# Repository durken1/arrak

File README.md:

# arrak
( unnecessarily weird) 36 key ergo keyboard

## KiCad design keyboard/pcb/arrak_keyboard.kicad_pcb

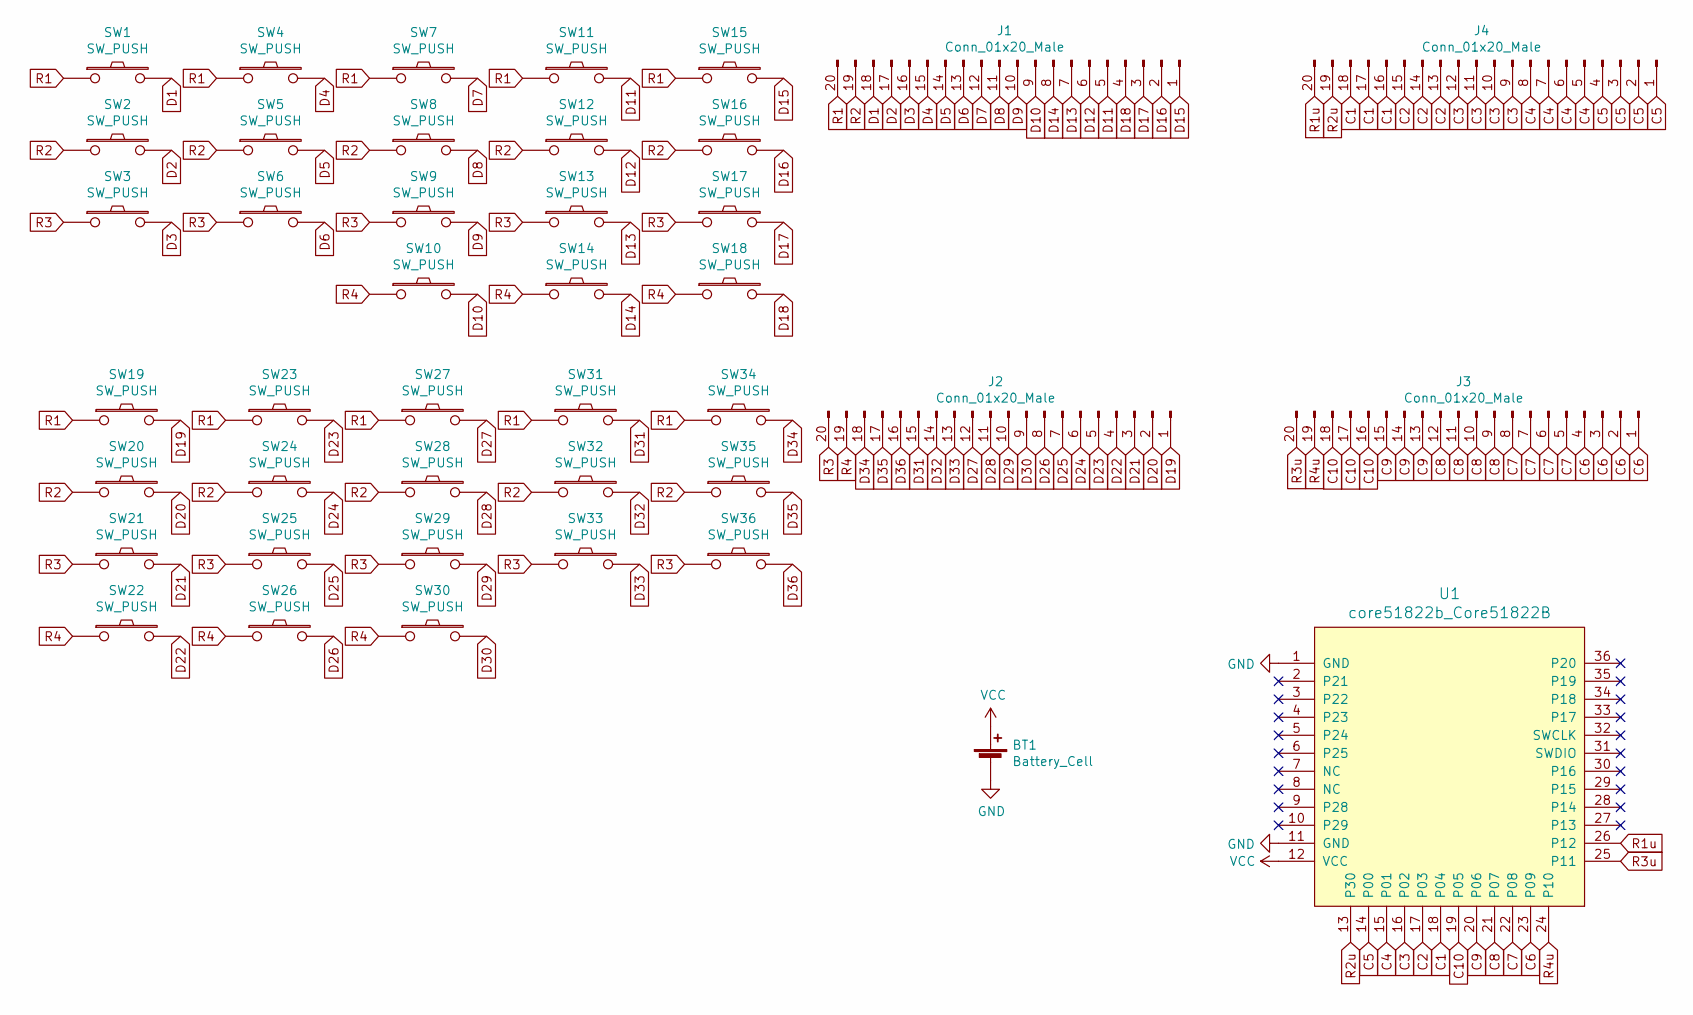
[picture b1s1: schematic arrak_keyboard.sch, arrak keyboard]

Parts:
BT1: Battery_Cell; BatteryHolder_Keystone_3034_1x20mm
J1, J2, J3, J4: Conn_01x20_Male; PinHeader_1x20_P2.54mm_Vertical
SW1, SW2, SW3, SW4, SW5, SW6, SW7, SW8, SW9, SW10, SW11, SW12, SW13, SW14, SW15, SW16, SW17, SW18, SW19, SW20, SW21, SW22, SW23, SW24, SW25, SW26, SW27, SW28, SW29, SW30, SW31, SW32, SW33, SW34, SW35, SW36: SW_PUSH; Kailh-PG1350-1u-reversible-NoLED
U1: core51822b_Core51822B; MY-YJ-14015-Module

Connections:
C1: J4.16, J4.17, J4.18, U1.18 (P04)
C2: J4.13, J4.14, J4.15, U1.17 (P03)
C3: J4.9, J4.10, J4.11, J4.12, U1.16 (P02)
C4: J4.5, J4.6, J4.7, J4.8, U1.15 (P01)
C5: J4.1, J4.2, J4.3, J4.4, U1.14 (P00)
C6: J3.1, J3.2, J3.3, J3.4, U1.23 (P09)
C7: J3.5, J3.6, J3.7, J3.8, U1.22 (P08)
C8: J3.9, J3.10, J3.11, J3.12, U1.21 (P07)
C9: J3.13, J3.14, J3.15, U1.20 (P06)
C10: J3.16, J3.17, J3.18, U1.19 (P05)
D1: J1.18, SW1.2
D2: J1.17, SW2.2
D3: J1.16, SW3.2
D4: J1.15, SW4.2
D5: J1.14, SW5.2
D6: J1.13, SW6.2
D7: J1.12, SW7.2
D8: J1.11, SW8.2
D9: J1.10, SW9.2
D10: J1.9, SW10.2
D11: J1.5, SW11.2
D12: J1.6, SW12.2
D13: J1.7, SW13.2
D14: J1.8, SW14.2
D15: J1.1, SW15.2
D16: J1.2, SW16.2
D17: J1.3, SW17.2
D18: J1.4, SW18.2
D19: J2.1, SW19.2
D20: J2.2, SW20.2
D21: J2.3, SW21.2
D22: J2.4, SW22.2
D23: J2.5, SW23.2
D24: J2.6, SW24.2
D25: J2.7, SW25.2
D26: J2.8, SW26.2
D27: J2.12, SW27.2
D28: J2.11, SW28.2
D29: J2.10, SW29.2
D30: J2.9, SW30.2
D31: J2.15, SW31.2
D32: J2.14, SW32.2
D33: J2.13, SW33.2
D34: J2.18, SW34.2
D35: J2.17, SW35.2
D36: J2.16, SW36.2
GND: BT1.2 (-), U1.1 (GND), U1.11 (GND)
R1: J1.20, SW1.1, SW4.1, SW7.1, SW11.1, SW15.1, SW19.1, SW23.1, SW27.1, SW31.1, SW34.1
R1u: J4.20, U1.26 (P12)
R2: J1.19, SW2.1, SW5.1, SW8.1, SW12.1, SW16.1, SW20.1, SW24.1, SW28.1, SW32.1, SW35.1
R2u: J4.19, U1.13 (P30)
R3: J2.20, SW3.1, SW6.1, SW9.1, SW13.1, SW17.1, SW21.1, SW25.1, SW29.1, SW33.1, SW36.1
R3u: J3.20, U1.25 (P11)
R4: J2.19, SW10.1, SW14.1, SW18.1, SW22.1, SW26.1, SW30.1
R4u: J3.19, U1.24 (P10)
VCC: BT1.1 (+), U1.12 (VCC)

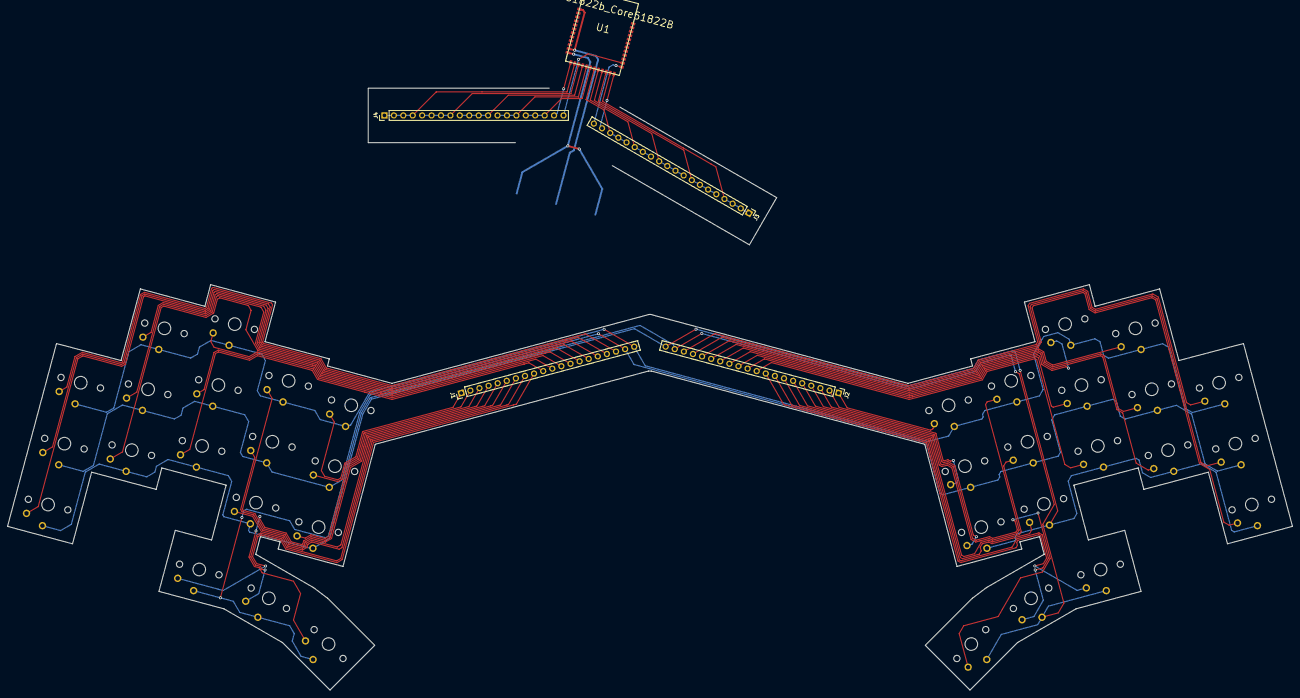
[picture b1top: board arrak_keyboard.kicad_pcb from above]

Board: 2 copper layers, 346.3 x 109.3 mm, 42 parts (1 on the bottom side), 56 nets.

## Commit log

2021-08-13 placement of switch footprints complete
2021-09-01 finish physical layout of keyboard?
2021-09-01 weird routing
2021-09-01 lite bättre routing
2021-09-09 finish keyboard pcb
2021-09-10 routing on wf module done
2021-09-10 add .gitignore
2021-09-10 add readme
